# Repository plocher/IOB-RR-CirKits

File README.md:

# IOB-RR-CirKits
## License: CERN Open Hardware Licence v1.2

IOB Interface with an 8-bit RR-CirKits-style 2x5 (10-pin) ribbon cable connector

  * Dual-size daughterboard
  * generic Input/Output passive adapter
  * Provisions for inline resistors (required cutting small traces to enable)

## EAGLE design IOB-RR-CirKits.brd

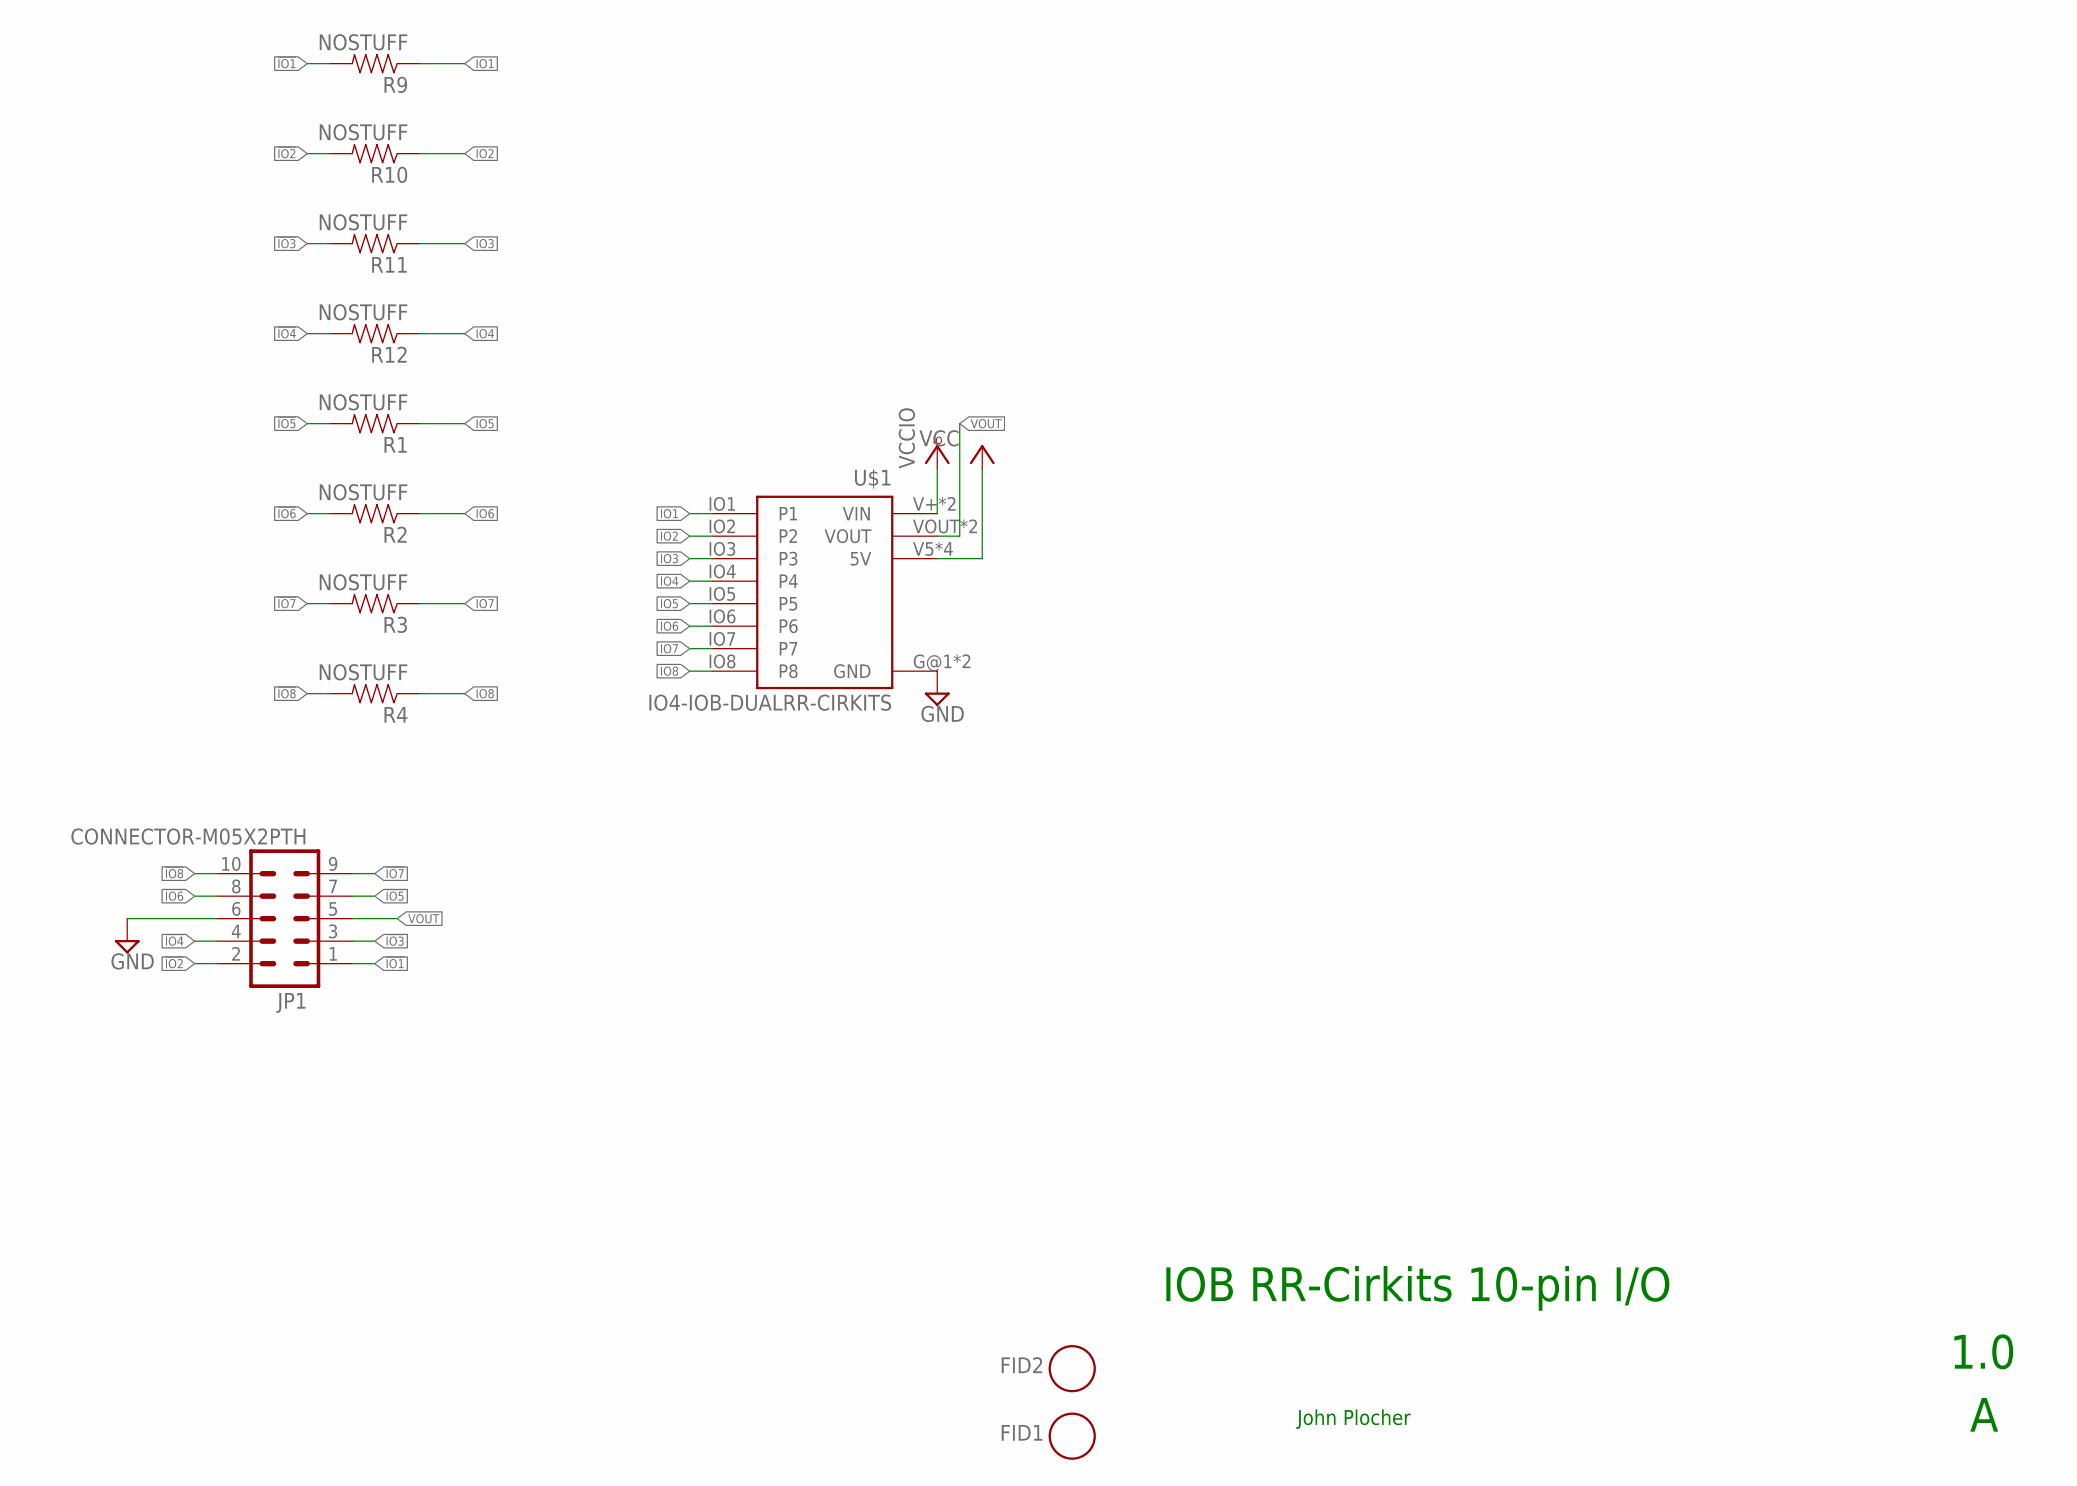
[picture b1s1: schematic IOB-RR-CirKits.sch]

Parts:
FID1, FID2: FIDUCIAL; FIDUCIAL_1MM
JP1: CONNECTOR-M05X2PTH; AVR_ICSP
R1, R2, R3, R4, R9, R10, R11, R12: NOSTUFF; CUT-R
U$1: IO4-IOB-DUALRR-CIRKITS; 10X-IOB

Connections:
!IO1: JP1.1, R9.P1 (2)
!IO2: JP1.2, R10.P1 (2)
!IO3: JP1.3, R11.P1 (2)
!IO4: JP1.4, R12.P1 (2)
!IO5: JP1.7, R1.P1 (2)
!IO6: JP1.8, R2.P1 (2)
!IO7: JP1.9, R3.P1 (2)
!IO8: JP1.10, R4.P1 (2)
GND: JP1.6, U$1.G@1 (GND), U$1.G@3 (GND)
IO1: R9.P2 (1), U$1.IO1 (P1)
IO2: R10.P2 (1), U$1.IO2 (P2)
IO3: R11.P2 (1), U$1.IO3 (P3)
IO4: R12.P2 (1), U$1.IO4 (P4)
IO5: R1.P2 (1), U$1.IO5 (P5)
IO6: R2.P2 (1), U$1.IO6 (P6)
IO7: R3.P2 (1), U$1.IO7 (P7)
IO8: R4.P2 (1), U$1.IO8 (P8)
VCC: U$1.V5 (5V), U$1.V5@1 (5V), U$1.V5@2 (5V), U$1.V5@3 (5V)
VCCIO: U$1.V+ (VIN), U$1.V+@1 (VIN)
VOUT: JP1.5, U$1.VOUT, U$1.VOUT@1 (VOUT)

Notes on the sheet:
IOB RR-Cirkits 10-pin I/O
1.0
John Plocher

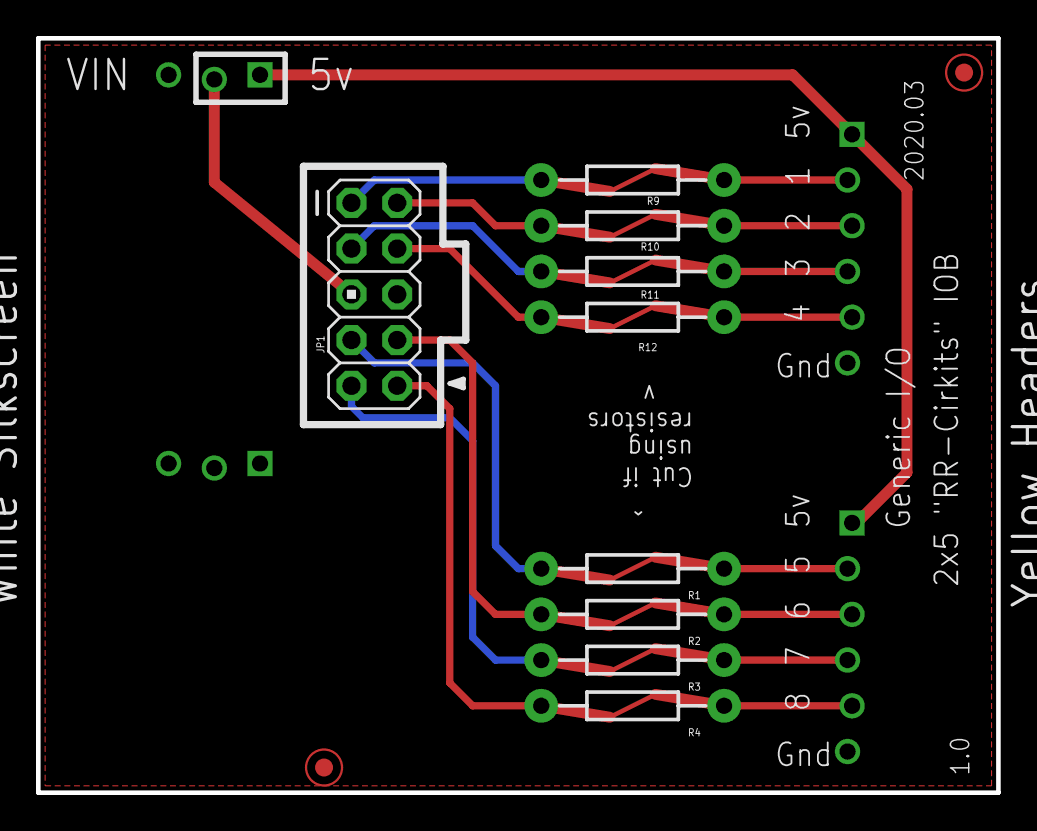
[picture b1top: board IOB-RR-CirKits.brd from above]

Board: 2 copper layers, 53.3 x 41.9 mm, 12 parts (0 on the bottom side), 20 nets.

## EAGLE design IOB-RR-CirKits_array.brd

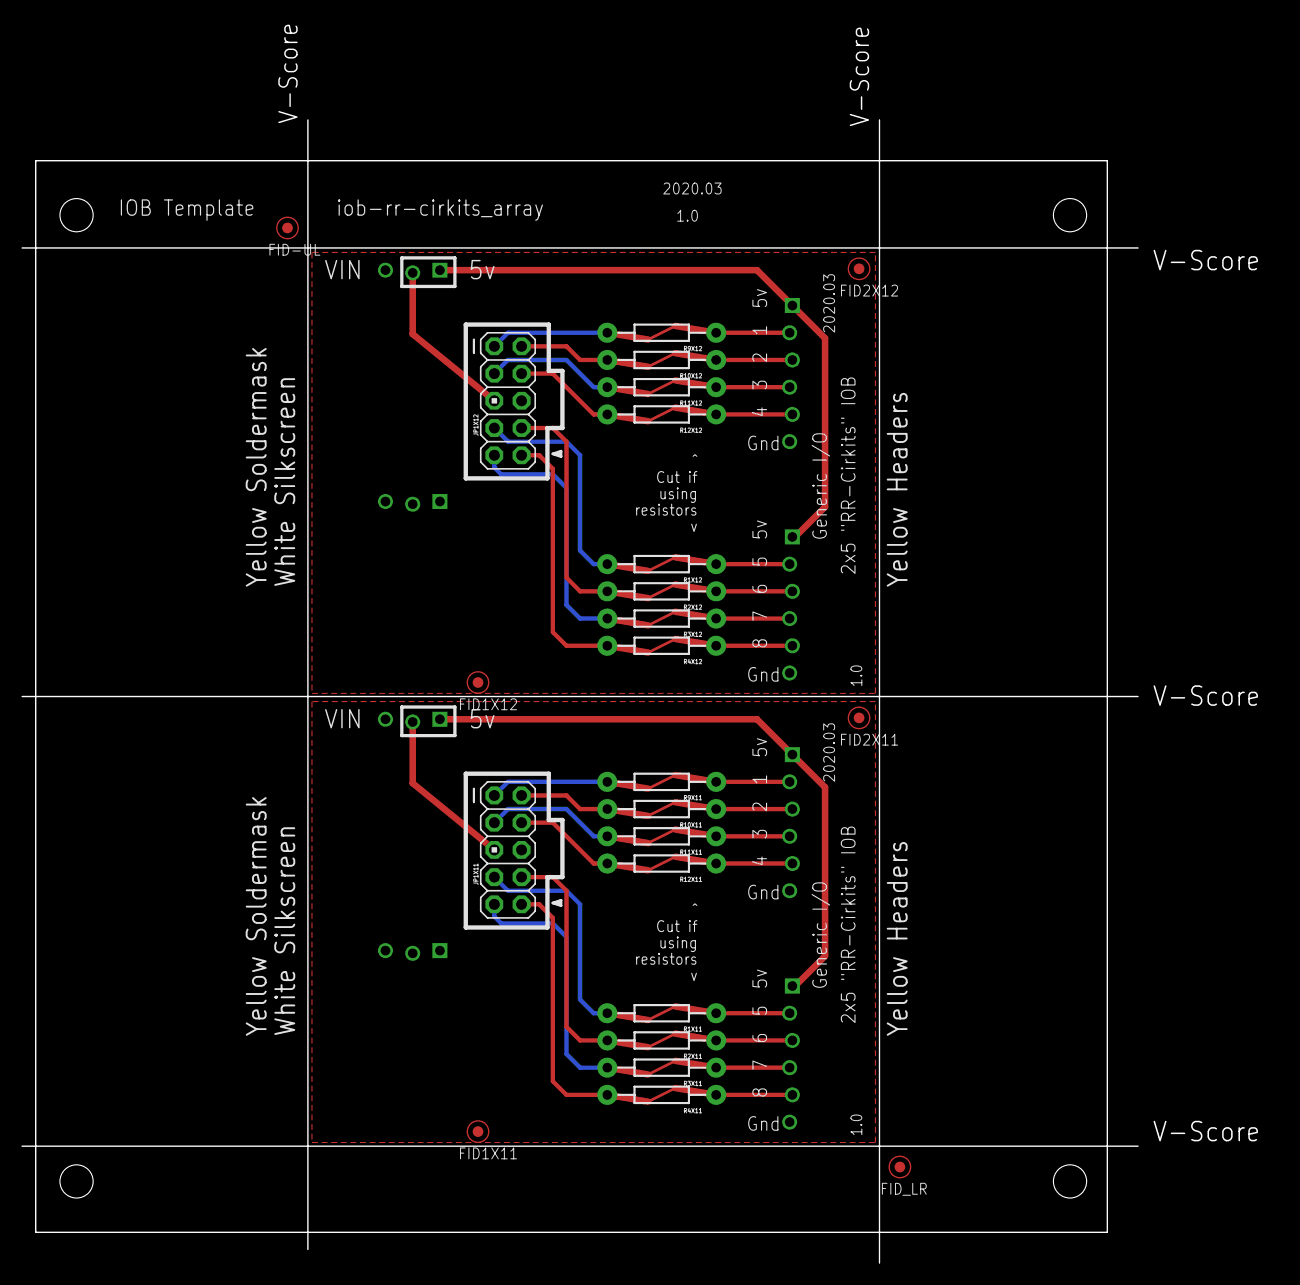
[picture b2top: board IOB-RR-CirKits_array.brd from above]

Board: 2 copper layers, 117.2 x 115.8 mm, 27 parts (0 on the bottom side), 40 nets.

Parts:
FID1X11, FID1X12, FID2X11, FID2X12: FIDUCIAL; FIDUCIAL_1MM
FID-UL: FIDUCIAL; FIDUCIAL_1MM
FID_LR: FIDUCIAL; FIDUCIAL_1MM
JP1X11, JP1X12: CONNECTOR-M05X2PTH; AVR_ICSP
R1X11, R1X12, R2X11, R2X12, R3X11, R3X12, R4X11, R4X12, R9X11, R9X12, R10X11, R10X12, R11X11, R11X12, R12X11, R12X12: NOSTUFF; CUT-R
U$1X1: BOARD-DINRAIL-3.17IN-H2X-IOB
U$1X11, U$1X12: IO4-IOB-DUALRR-CIRKITS; 10X-IOB

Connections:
!IO1X11: JP1X11.1, R9X11.P1
!IO1X12: JP1X12.1, R9X12.P1
!IO2X11: JP1X11.2, R10X11.P1
!IO2X12: JP1X12.2, R10X12.P1
!IO3X11: JP1X11.3, R11X11.P1
!IO3X12: JP1X12.3, R11X12.P1
!IO4X11: JP1X11.4, R12X11.P1
!IO4X12: JP1X12.4, R12X12.P1
!IO5X11: JP1X11.7, R1X11.P1
!IO5X12: JP1X12.7, R1X12.P1
!IO6X11: JP1X11.8, R2X11.P1
!IO6X12: JP1X12.8, R2X12.P1
!IO7X11: JP1X11.9, R3X11.P1
!IO7X12: JP1X12.9, R3X12.P1
!IO8X11: JP1X11.10, R4X11.P1
!IO8X12: JP1X12.10, R4X12.P1
GNDX11: JP1X11.6, U$1X11.G@1, U$1X11.G@3
GNDX12: JP1X12.6, U$1X12.G@1, U$1X12.G@3
IO1X11: R9X11.P2, U$1X11.IO1
IO1X12: R9X12.P2, U$1X12.IO1
IO2X11: R10X11.P2, U$1X11.IO2
IO2X12: R10X12.P2, U$1X12.IO2
IO3X11: R11X11.P2, U$1X11.IO3
IO3X12: R11X12.P2, U$1X12.IO3
IO4X11: R12X11.P2, U$1X11.IO4
IO4X12: R12X12.P2, U$1X12.IO4
IO5X11: R1X11.P2, U$1X11.IO5
IO5X12: R1X12.P2, U$1X12.IO5
IO6X11: R2X11.P2, U$1X11.IO6
IO6X12: R2X12.P2, U$1X12.IO6
IO7X11: R3X11.P2, U$1X11.IO7
IO7X12: R3X12.P2, U$1X12.IO7
IO8X11: R4X11.P2, U$1X11.IO8
IO8X12: R4X12.P2, U$1X12.IO8
VCCIOX11: U$1X11.V+, U$1X11.V+@1
VCCIOX12: U$1X12.V+, U$1X12.V+@1
VCCX11: U$1X11.V5, U$1X11.V5@1, U$1X11.V5@2, U$1X11.V5@3
VCCX12: U$1X12.V5, U$1X12.V5@1, U$1X12.V5@2, U$1X12.V5@3
VOUTX11: JP1X11.5, U$1X11.VOUT, U$1X11.VOUT@1
VOUTX12: JP1X12.5, U$1X12.VOUT, U$1X12.VOUT@1

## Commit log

2020-03-04 Initial version
2020-03-05 added 2-up array
2020-03-07 updated changelog
2020-05-04 updated tags
2020-08-11 normalized silkscreen layout across IOBs
2020-08-11 move text from DOCU to TPLACE
2020-08-11 added csv files
